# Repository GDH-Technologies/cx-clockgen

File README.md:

# cx-clockgen
Essentially a fork of Rene Wolf's `cxadc-clock-generator-audio-adc` gitlab project

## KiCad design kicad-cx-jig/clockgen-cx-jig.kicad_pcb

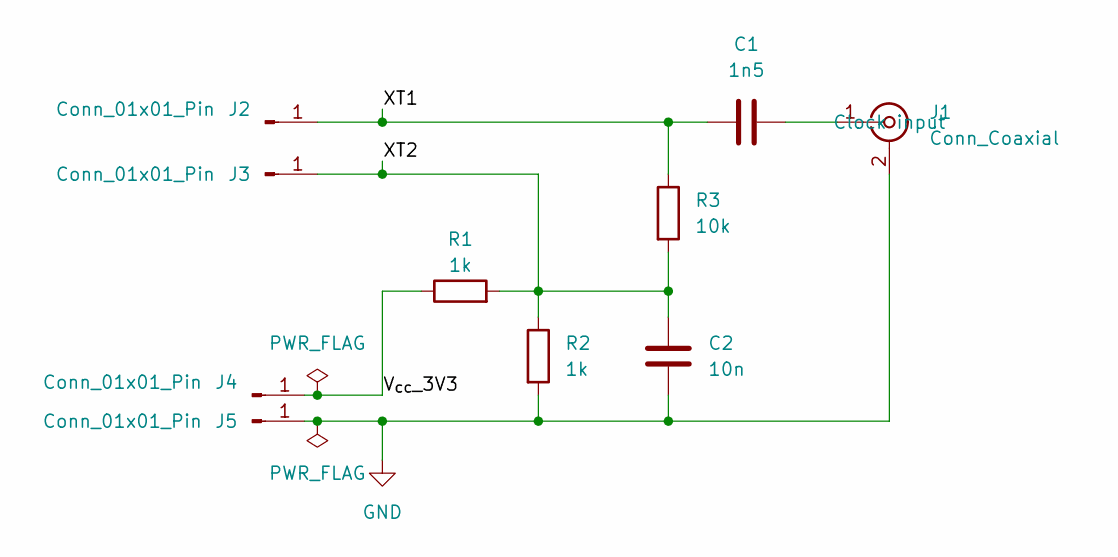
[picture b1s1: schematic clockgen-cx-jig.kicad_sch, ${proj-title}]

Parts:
C1: 1n5; C_0805_2012Metric_Pad1.18x1.45mm_HandSolder
C2: 10n; C_0805_2012Metric_Pad1.18x1.45mm_HandSolder
J1: Conn_Coaxial; SMA_Samtec_SMA-J-P-H-ST-EM1_EdgeMount
J2, J3, J4, J5: Conn_01x01_Pin; TestPoint_Pad_D2.0mm
R1, R2: 1k; R_0805_2012Metric_Pad1.20x1.40mm_HandSolder
R3: 10k; R_0805_2012Metric_Pad1.20x1.40mm_HandSolder

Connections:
/V_{cc}_3V3: J4.1 (Pin_1_1), R1.1
/XT1: C1.2, J2.1 (Pin_1_1), R3.1
/XT2: C2.1, J3.1 (Pin_1_1), R1.2, R2.1, R3.2
GND: C2.2, J1.2 (Ext), J5.1 (Pin_1_1), R2.2
unnamed: C1.1, J1.1 (In)

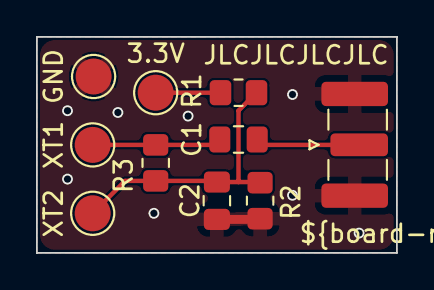
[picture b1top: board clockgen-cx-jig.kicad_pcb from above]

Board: 2 copper layers, 20.0 x 12.0 mm, 11 parts (0 on the bottom side), 5 nets.

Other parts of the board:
${board-ref}**: Board

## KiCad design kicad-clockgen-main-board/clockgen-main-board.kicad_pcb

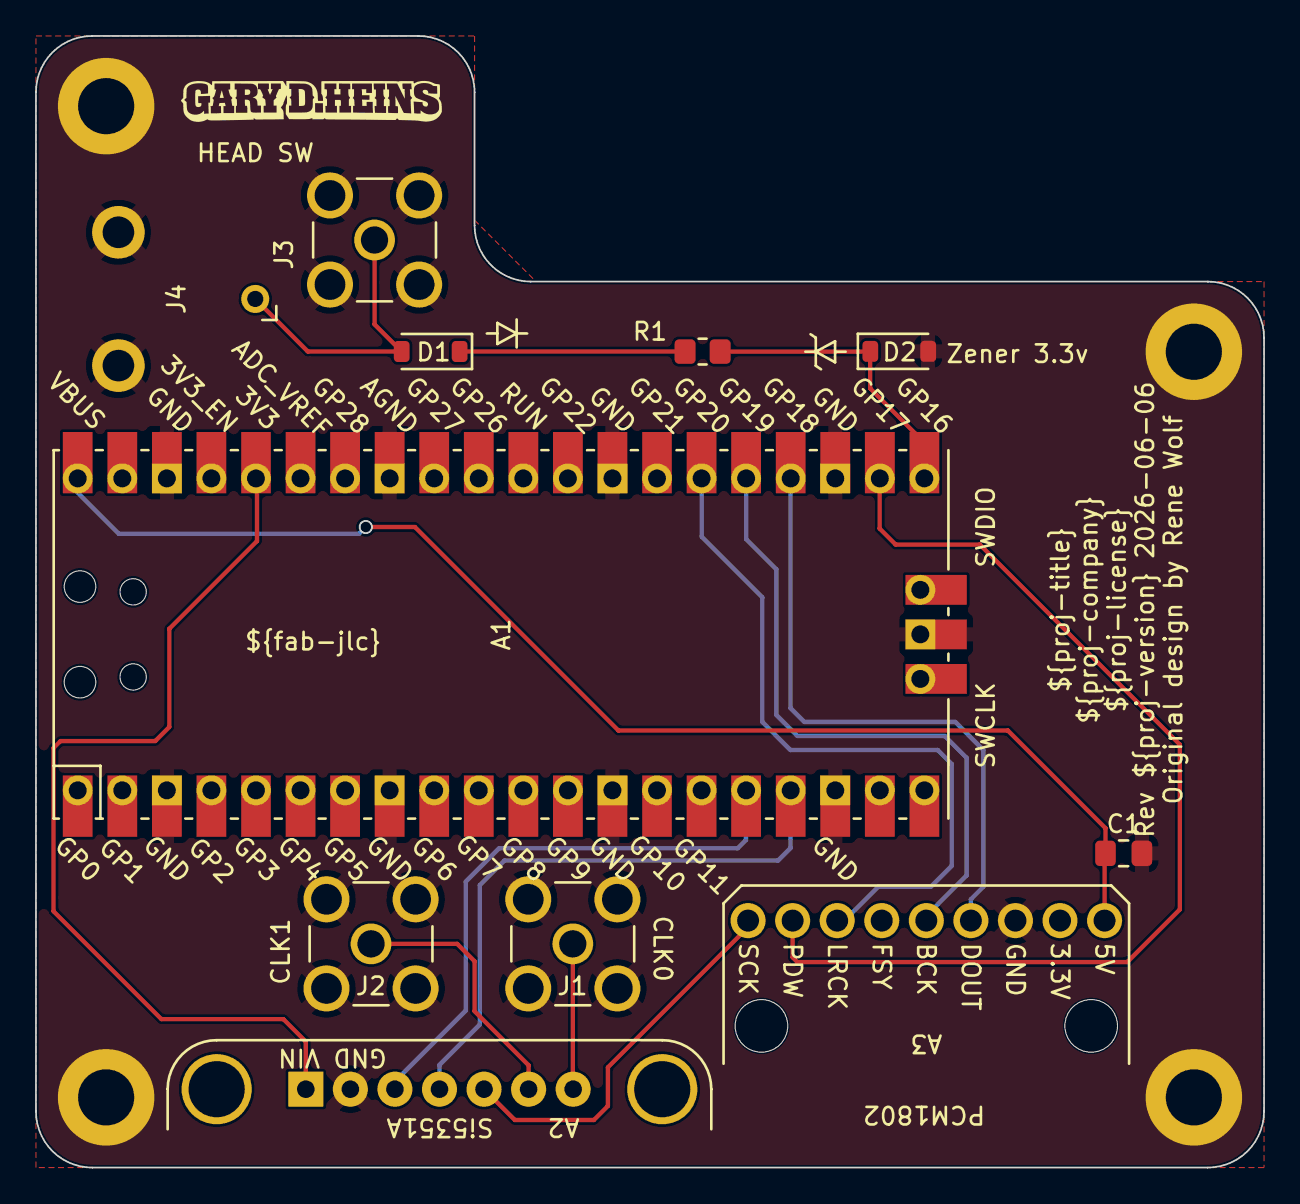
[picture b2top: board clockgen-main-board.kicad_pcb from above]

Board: 2 copper layers, 70.0 x 64.5 mm, 16 parts (0 on the bottom side), 15 nets.

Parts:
${board-ref}**: Board
A1: Pico; Pi_Pico_SMD_TH
A2: Si5351A; Adafruit_Si5351A_Breakout_Board
A3: PCM1802; black-pcm1802-board
C1: 10u; C_0805_2012Metric_Pad1.18x1.45mm_HandSolder
D1: D; D_SOD-123
D2: D_Zener; D_SOD-123
H1, H2, H3, H4: MountingHole_Pad; MountingHole_3.2mm_M3_ISO14580_Pad
J1: CLK0_SMA; GRADCONN_RFPC-SMA28-F
J2: CLK1_SMA; GRADCONN_RFPC-SMA28-F
J3: Headswitch_SMA; GRADCONN_RFPC-SMA28-F
J4: Headswitch_BNC; Molex_0731000154_BNC_RA_THT
R1: 1k; R_0805_2012Metric_Pad1.20x1.40mm_HandSolder

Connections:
/Gen.SCL: A1.17 (GPIO13), A2.3 (SCL)
/Gen.SDA: A1.16 (GPIO12), A2.4 (SDA)
/Gen.VSI: A1.36 (3V3), A2.6 (VIN)
/Head_SW_In: D1.2 (A), J3.1, J4.1 (In)
/PCM.5V: A1.40 (VBUS), A3.1 (+5V), C1.1
/PCM.BitClk: A1.25 (GPIO19), A3.5 (BCK)
/PCM.Data: A1.24 (GPIO18), A3.4 (DOUT)
/PCM.LRClk: A1.26 (GPIO20), A3.7 (LRCK)
/PCM.PwrDn: A1.22 (GPIO17), A3.8 (PDW)
/PCM.SysClk: A2.2 (CLK2), A3.9 (SCK)
GND: A1.3 (GND), A1.8 (GND), A1.13 (GND), A1.18 (GND), A1.23 (GND), A1.28 (GND), A1.33 (AGND), A1.38 (GND), A1.42 (GND), A2.5 (GND), A3.3 (GND), C1.2, D2.2 (A), H1.1 (1_1), H2.1 (1_1), H3.1 (1_1), H4.1 (1_1), J1.2 (GND_2), J2.2 (GND_2), J3.2 (GND_2), J4.2 (Ext)
unnamed: A1.21 (GPIO16), D2.1 (K), R1.2
unnamed: A2.0 (CLK0), J1.1
unnamed: A2.1 (CLK1), J2.1
unnamed: D1.1 (K), R1.1

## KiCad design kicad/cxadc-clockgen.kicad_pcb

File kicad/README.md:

This is a test project to see how design blocks work

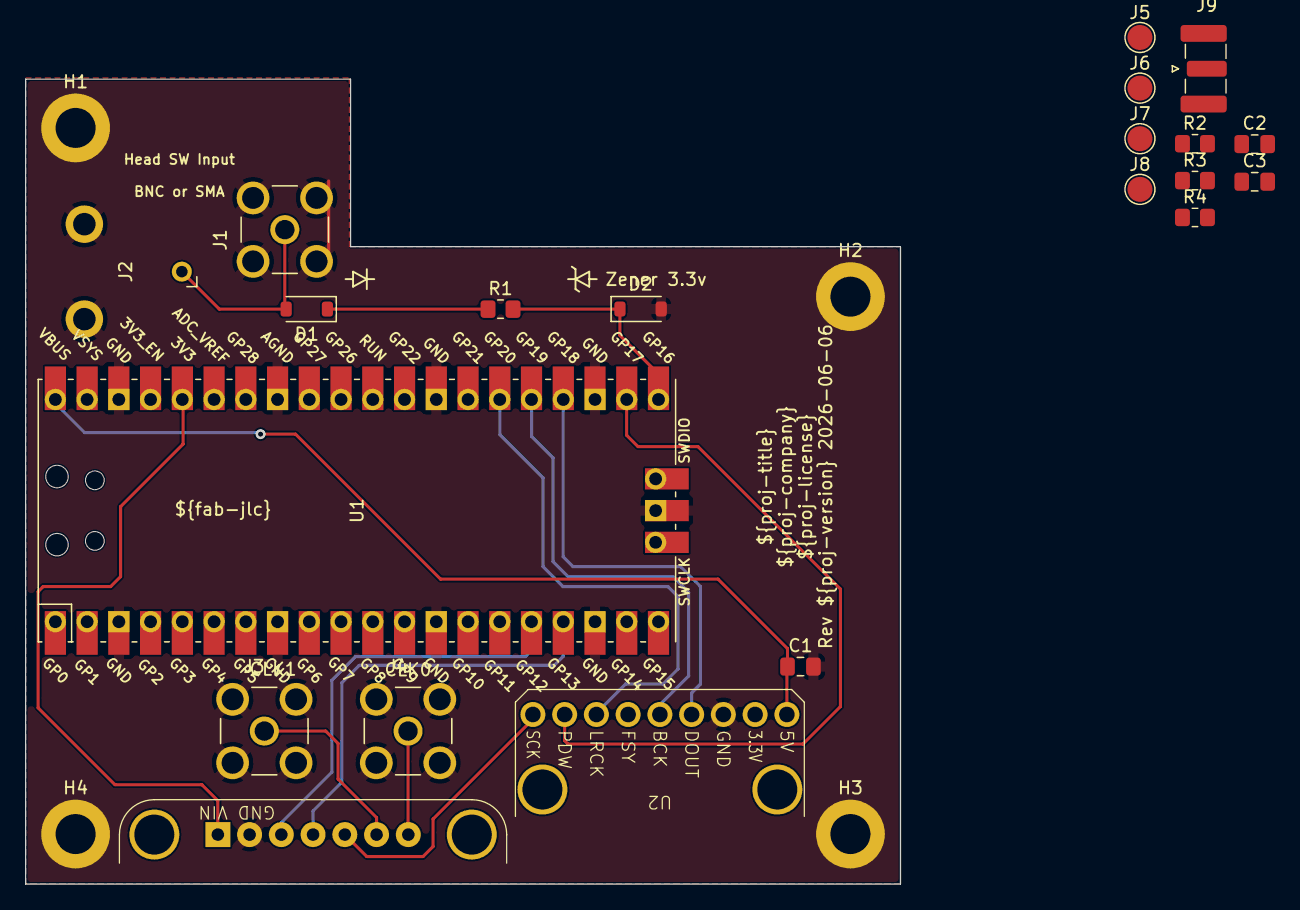
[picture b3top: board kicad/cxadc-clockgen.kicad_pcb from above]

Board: 2 copper layers, 70.0 x 64.4 mm, 25 parts (0 on the bottom side), 19 nets.

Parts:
C1: 10u; C_0805_2012Metric_Pad1.18x1.45mm_HandSolder
C2: 10n; C_0805_2012Metric_Pad1.18x1.45mm_HandSolder
C3: 1n5; C_0805_2012Metric_Pad1.18x1.45mm_HandSolder
D1: D; D_SOD-123
D2: D_Zener; D_SOD-123
H1, H2, H3, H4: MountingHole_Pad; MountingHole_3.2mm_M3_ISO14580_Pad
J1: Headswitch_SMA; GRADCONN_RFPC-SMA28-F
J2: Conn_Coaxial; Molex_0731000154_BNC_RA_THT
J3, J4: Conn_01x03_Pin; GRADCONN_RFPC-SMA28-F
J5, J6, J7, J8: Conn_01x01_Pin; TestPoint_Pad_D2.0mm
J9: Conn_Coaxial; SMA_Samtec_SMA-J-P-H-ST-EM1_EdgeMount
R1, R2, R3: 1k; R_0805_2012Metric_Pad1.20x1.40mm_HandSolder
R4: 10k; R_0805_2012Metric_Pad1.20x1.40mm_HandSolder
U1: Pico; Pi_Pico_SMD_TH
U2: black-pcm1802-board
U3: Adafruit_Si5351A_Breakout_Board

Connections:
/Main Board/Gen.SCL: U1.17 (GPIO13), U3.3 (SCL)
/Main Board/Gen.SDA: U1.16 (GPIO12), U3.4 (SDA)
/Main Board/Gen.VSI: U1.36 (3V3), U3.6 (VIN)
/Main Board/Head_SW_In: D1.2 (A), J1.1, J2.1 (In)
/Main Board/PCM.5V: C1.1, U1.40 (VBUS), U2.1 (+5V)
/Main Board/PCM.BitClk: U1.25 (GPIO19), U2.5 (BCK)
/Main Board/PCM.Data: U1.24 (GPIO18), U2.4 (DOUT)
/Main Board/PCM.LRClk: U1.26 (GPIO20), U2.7 (LRCK)
/Main Board/PCM.PwrDn: U1.22 (GPIO17), U2.8 (PDW)
/Main Board/PCM.SysClk: U2.9 (SCK), U3.2 (CLK2)
/Video CX Jig/V_{cc}_3V3: J5.1 (Pin_1_1), R2.1
/Video CX Jig/XT1: C3.2, J7.1 (Pin_1_1), R4.1
/Video CX Jig/XT2: C2.1, J8.1 (Pin_1_1), R2.2, R3.1, R4.2
GND: C1.2, C2.2, D2.2 (A), H1.1 (1_1), H2.1 (1_1), H3.1 (1_1), H4.1 (1_1), J1.2 (GND_2), J2.2 (Ext), J3.2 (GND_2), J4.2 (GND_2), J6.1 (Pin_1_1), J9.2 (Ext), R3.2, U1.3 (GND), U1.8 (GND), U1.13 (GND), U1.18 (GND), U1.23 (GND), U1.28 (GND), U1.33 (AGND), U1.38 (GND), U1.42 (GND), U2.3 (GND), U3.5 (GND)
unnamed: D1.1 (K), R1.1
unnamed: D2.1 (K), R1.2, U1.21 (GPIO16)
unnamed: C3.1, J9.1 (In)
unnamed: J4.1, U3.0 (CLK0)
unnamed: J3.1, U3.1 (CLK1)

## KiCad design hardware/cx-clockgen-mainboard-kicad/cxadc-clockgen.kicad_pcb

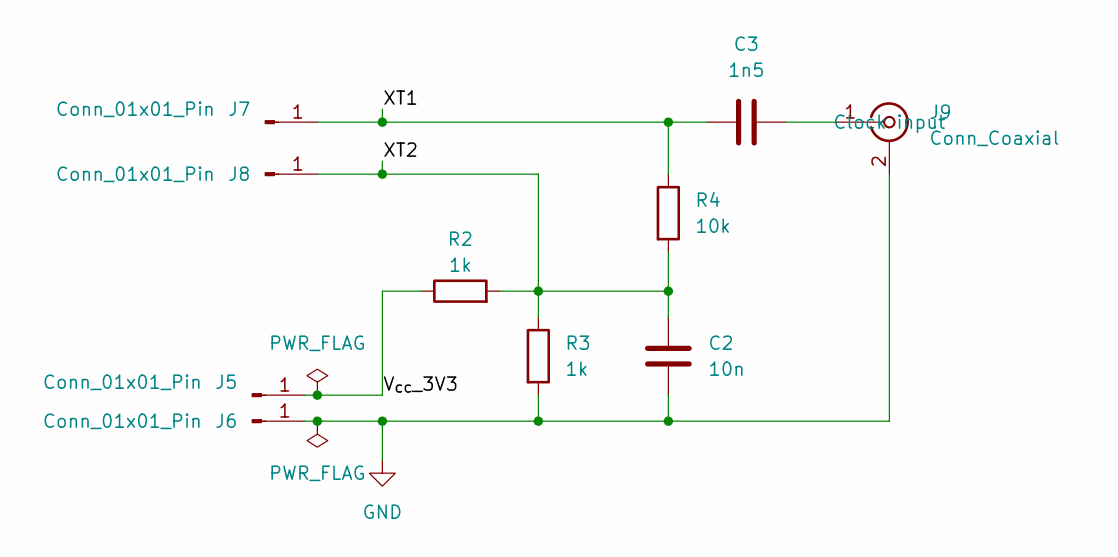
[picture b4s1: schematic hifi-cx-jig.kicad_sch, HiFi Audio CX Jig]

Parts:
C2: 10n; C_0805_2012Metric_Pad1.18x1.45mm_HandSolder
C3: 1n5; C_0805_2012Metric_Pad1.18x1.45mm_HandSolder
J5, J6, J7, J8: Conn_01x01_Pin; TestPoint_Pad_D2.0mm
J9: Conn_Coaxial; SMA_Samtec_SMA-J-P-H-ST-EM1_EdgeMount
R2, R3: 1k; R_0805_2012Metric_Pad1.20x1.40mm_HandSolder
R4: 10k; R_0805_2012Metric_Pad1.20x1.40mm_HandSolder

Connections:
/HiFi Audio CX Jig/V_{cc}_3V3: J5.1 (Pin_1_1), R2.1
/HiFi Audio CX Jig/XT1: C3.2, J7.1 (Pin_1_1), R4.1
/HiFi Audio CX Jig/XT2: C2.1, J8.1 (Pin_1_1), R2.2, R3.1, R4.2
GND: C2.2, J6.1 (Pin_1_1), J9.2 (Ext), R3.2; also elsewhere on the board
unnamed: C3.1, J9.1 (In)

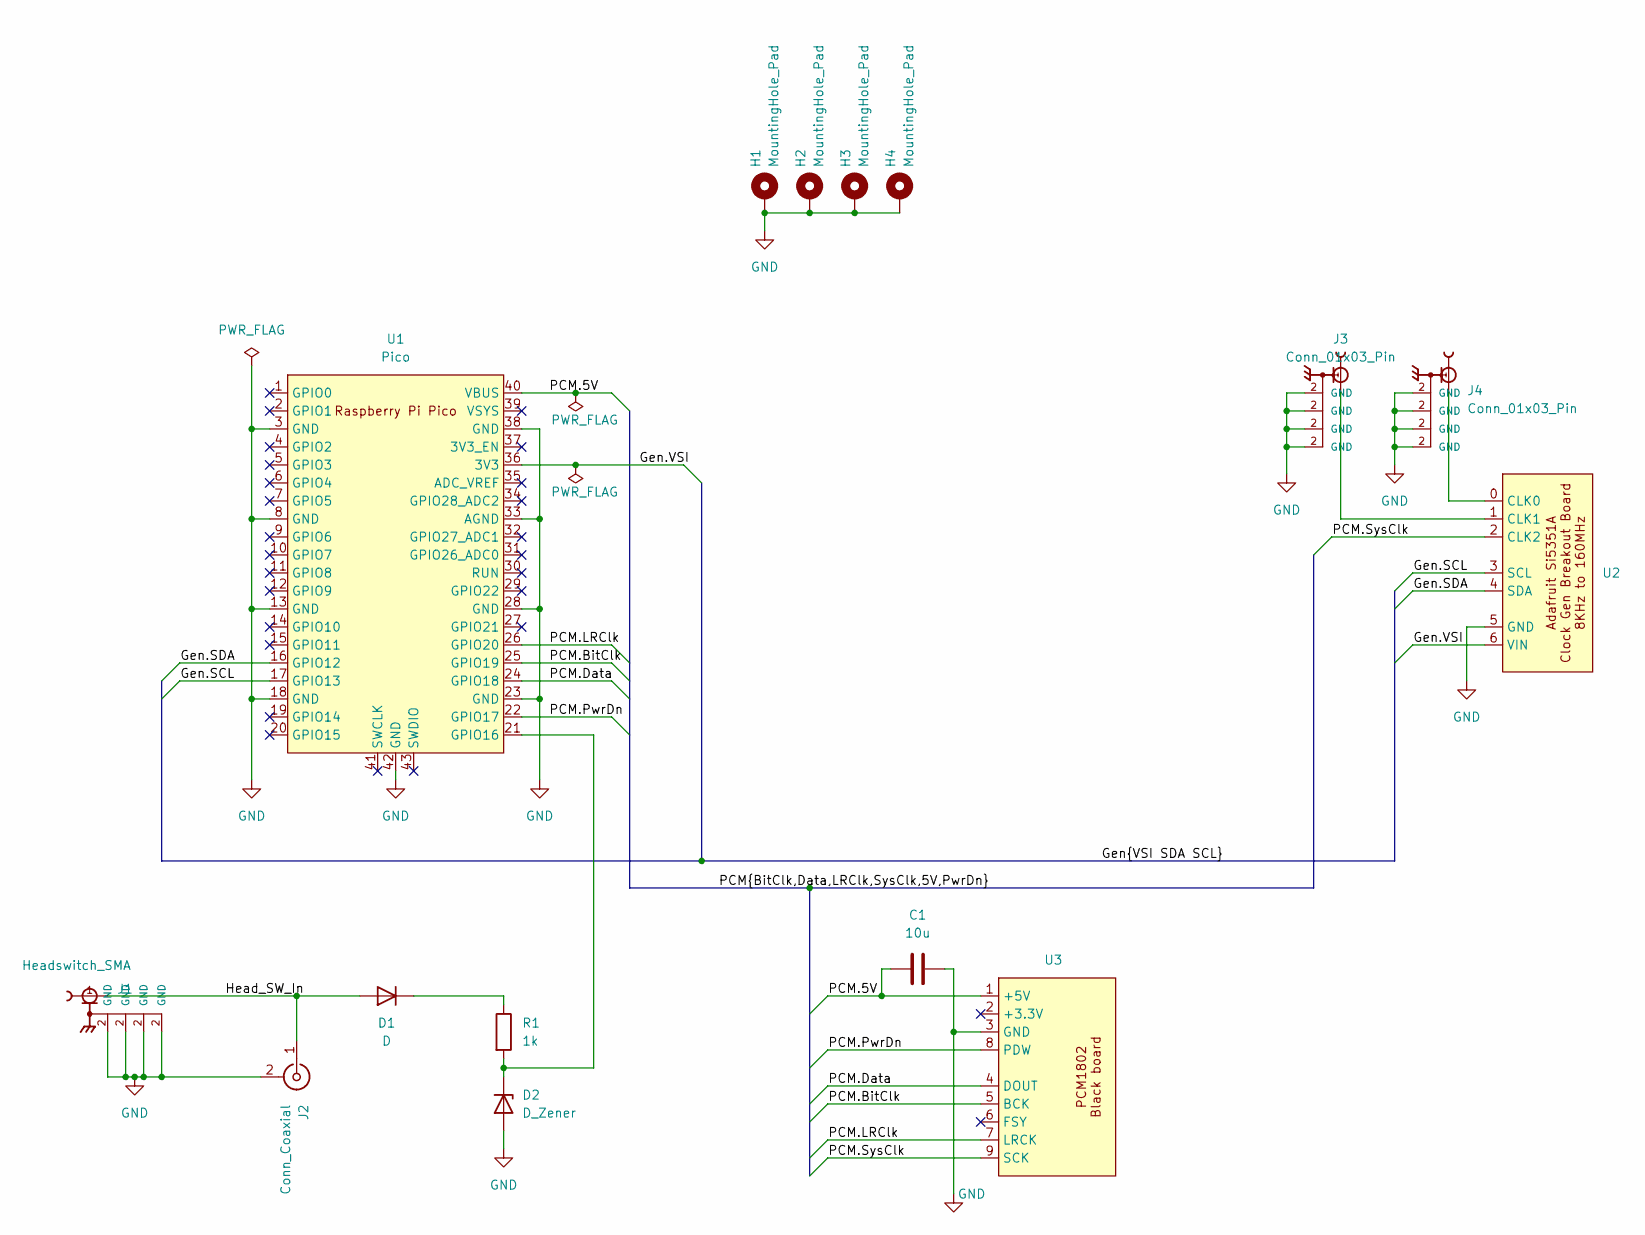
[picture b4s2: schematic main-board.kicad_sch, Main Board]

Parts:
C1: 10u; C_0805_2012Metric_Pad1.18x1.45mm_HandSolder
D1: D; D_SOD-123
D2: D_Zener; D_SOD-123
H1, H2, H3, H4: MountingHole_Pad; MountingHole_3.2mm_M3_ISO14580_Pad
J1: Headswitch_SMA; GRADCONN_RFPC-SMA28-F; PARTREV 1.0
J2: Conn_Coaxial; Molex_0731000154_BNC_RA_THT
J3, J4: Conn_01x03_Pin; GRADCONN_RFPC-SMA28-F; PARTREV 1.0
R1: 1k; R_0805_2012Metric_Pad1.20x1.40mm_HandSolder
U1: Pico; Pi_Pico_SMD_TH; MPN Raspberry Pi Pico
U2: Adafruit_Si5351A_Breakout_Board; MPN 2045
U3: black-pcm1802-board

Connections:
/Main Board/Gen.SCL: U1.17 (GPIO13), U2.3 (SCL)
/Main Board/Gen.SDA: U1.16 (GPIO12), U2.4 (SDA)
/Main Board/Gen.VSI: U1.36 (3V3), U2.6 (VIN)
/Main Board/Head_SW_In: D1.2 (A), J1.1, J2.1 (In)
/Main Board/PCM.5V: C1.1, U1.40 (VBUS), U3.1 (+5V)
/Main Board/PCM.BitClk: U1.25 (GPIO19), U3.5 (BCK)
/Main Board/PCM.Data: U1.24 (GPIO18), U3.4 (DOUT)
/Main Board/PCM.LRClk: U1.26 (GPIO20), U3.7 (LRCK)
/Main Board/PCM.PwrDn: U1.22 (GPIO17), U3.8 (PDW)
/Main Board/PCM.SysClk: U2.2 (CLK2), U3.9 (SCK)
GND: C1.2, D2.2 (A), H1.1 (1_1), H2.1 (1_1), H3.1 (1_1), H4.1 (1_1), J1.2 (GND_2), J2.2 (Ext), J3.2 (GND_2), J4.2 (GND_2), U1.3 (GND), U1.8 (GND), U1.13 (GND), U1.18 (GND), U1.23 (GND), U1.28 (GND), U1.33 (AGND), U1.38 (GND), U1.42 (GND), U2.5 (GND), U3.3 (GND); also elsewhere on the board
unnamed: D1.1 (K), R1.1
unnamed: D2.1 (K), R1.2, U1.21 (GPIO16)
unnamed: J4.1, U2.0 (CLK0)
unnamed: J3.1, U2.1 (CLK1)

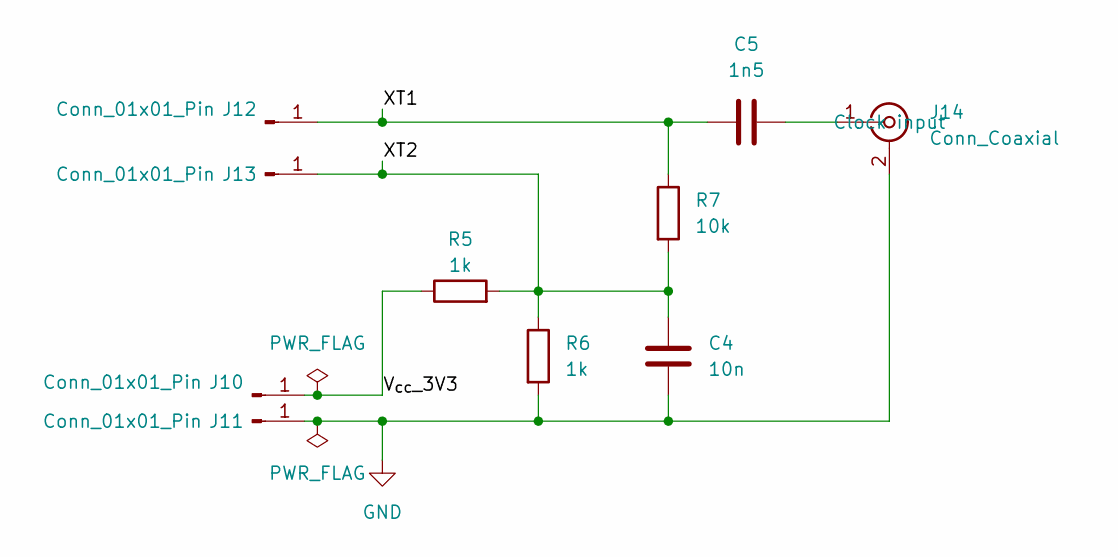
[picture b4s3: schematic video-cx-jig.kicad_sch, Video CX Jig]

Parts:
C4: 10n; C_0805_2012Metric_Pad1.18x1.45mm_HandSolder
C5: 1n5; C_0805_2012Metric_Pad1.18x1.45mm_HandSolder
J10, J11, J12, J13: Conn_01x01_Pin; TestPoint_Pad_D2.0mm
J14: Conn_Coaxial; SMA_Samtec_SMA-J-P-H-ST-EM1_EdgeMount
R5, R6: 1k; R_0805_2012Metric_Pad1.20x1.40mm_HandSolder
R7: 10k; R_0805_2012Metric_Pad1.20x1.40mm_HandSolder

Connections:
/Video CX Jig/V_{cc}_3V3: J10.1 (Pin_1_1), R5.1
/Video CX Jig/XT1: C5.2, J12.1 (Pin_1_1), R7.1
/Video CX Jig/XT2: C4.1, J13.1 (Pin_1_1), R5.2, R6.1, R7.2
GND: C4.2, J11.1 (Pin_1_1), J14.2 (Ext), R6.2; also elsewhere on the board
unnamed: C5.1, J14.1 (In)

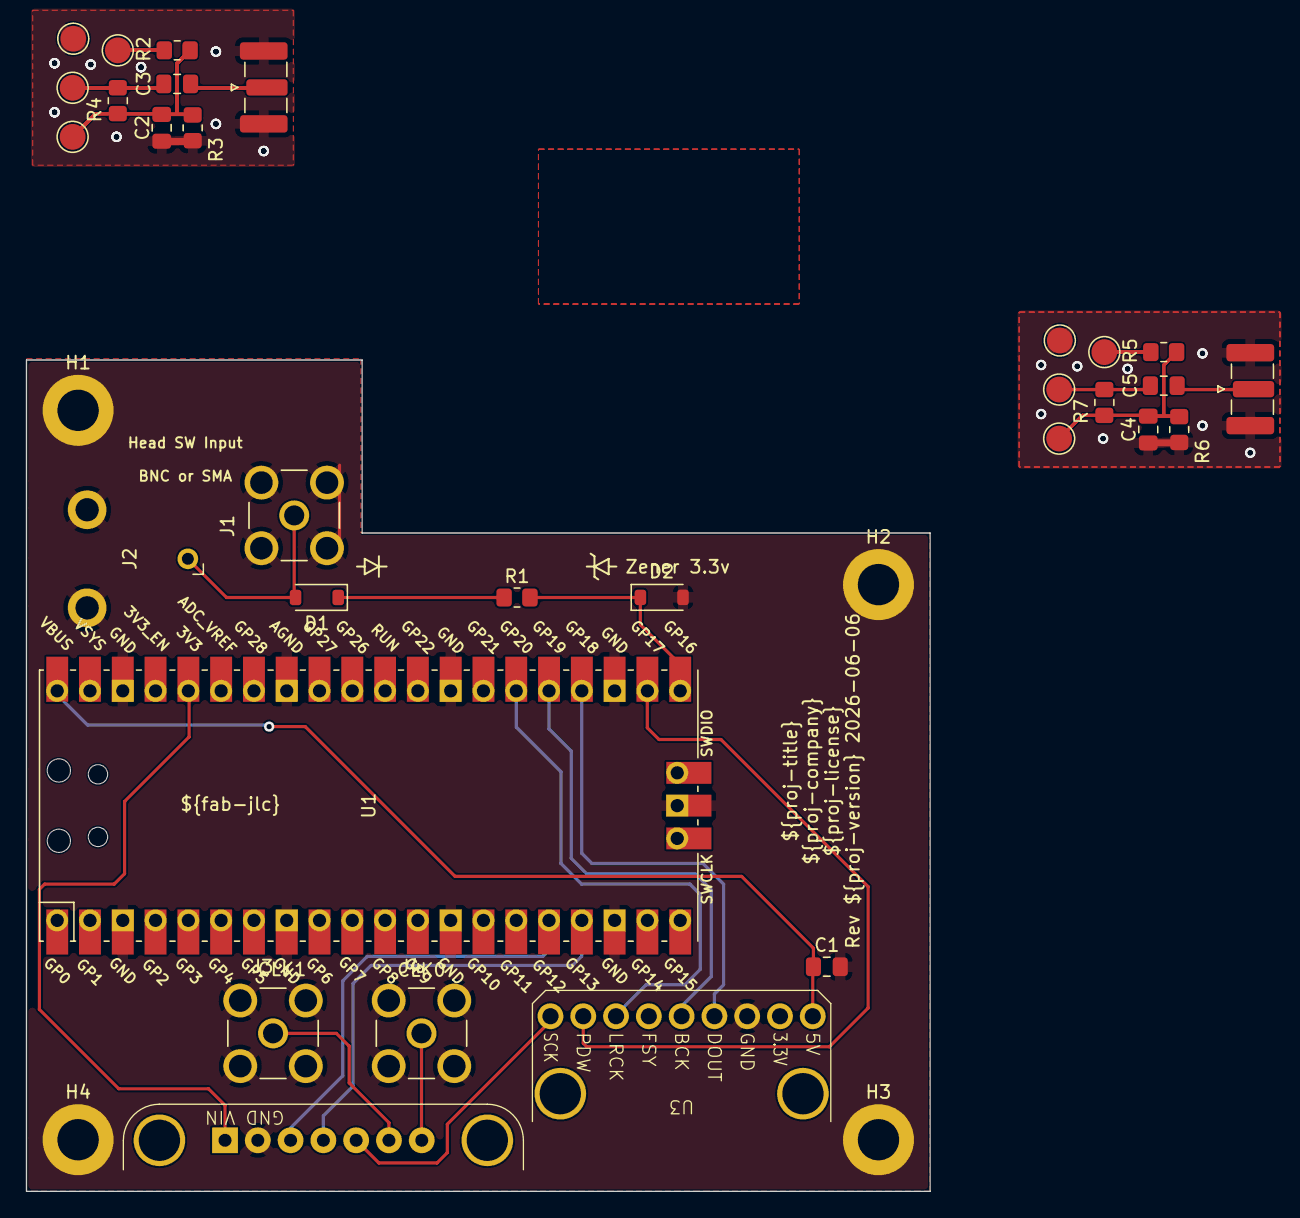
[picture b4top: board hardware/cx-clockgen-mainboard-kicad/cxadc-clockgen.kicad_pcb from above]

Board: 2 copper layers, 70.0 x 64.4 mm, 35 parts (0 on the bottom side), 23 nets.

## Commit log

2026-04-28 Added main board and cx jig kicard projects
2026-04-28 Added missing folders
2026-04-28 Added missing setup shell scripts
2026-05-10 Updated build and installation scripts for improved functionality and error handling; added new package installation logic for Debian and Fedora, enhanced logging, and refined project settings in KiC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
2026-06-05 Updated KiCad project files to version 20260206, improved tenting and covering settings, and added new parameters for zone clearance. Modified footprint and net definitions for better clarity. Enhanc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
2026-06-05 Updated KiCad project files: set schematic revision to project version, changed pin-to-pin error handling, updated UUID, and modified component properties for better visibility and placement control.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
2026-06-06 Remove obsolete KiCad library files, including symbol, footprint, and 3D model files for ADA4857-1YRZ-R7 and related components, to streamline project resources and eliminate unused assets.
2026-06-06 Update KiCad project files: corrected project title and version, replaced embedded model paths with environment variable references, and removed obsolete render image to streamline project resources.
2026-06-06 Update KiCad project files: modified project title and version, adjusted component properties, and streamlined pin functions for clarity. Removed obsolete library references and updated netlist handl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
2026-06-06 Remove obsolete KiCad project files for the clock generator main board, including DRC, ERC, DRU, PCB, schematic, and project configuration files. Updated the CX Jig project files with new author and 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
2026-06-08 refactor: Split combined main board + jig project into discrete ones
2026-06-08 Add initial fp-lib-table and sym-lib-table for KiCad project
    - Created fp-lib-table with version 7 for footprint libraries.
    - Created sym-lib-table with version 7 for symbol libraries.
2026-06-09 Add Gerber file for clockgen-cx-jig front silkscreen layer
2026-06-11 Update design rules and constraints in KiCad project
    - Changed hole_to_hole check from error to warning.
    - Updated npth_inside_courtyard and pth_inside_courtyard checks to error.
    - Set silk_over_copper and silk_overlap checks to ignore.
    - Adjusted various minimum clearance and connection rules for better compliance.
    - Modified teardrop parameters to reduce curve segment count.
    - Added new track widths and updated via dimensions.
2026-06-12 Add board reference variable to project configuration

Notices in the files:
parts and their libraries:
proj-license: CC BY-SA 4.0
